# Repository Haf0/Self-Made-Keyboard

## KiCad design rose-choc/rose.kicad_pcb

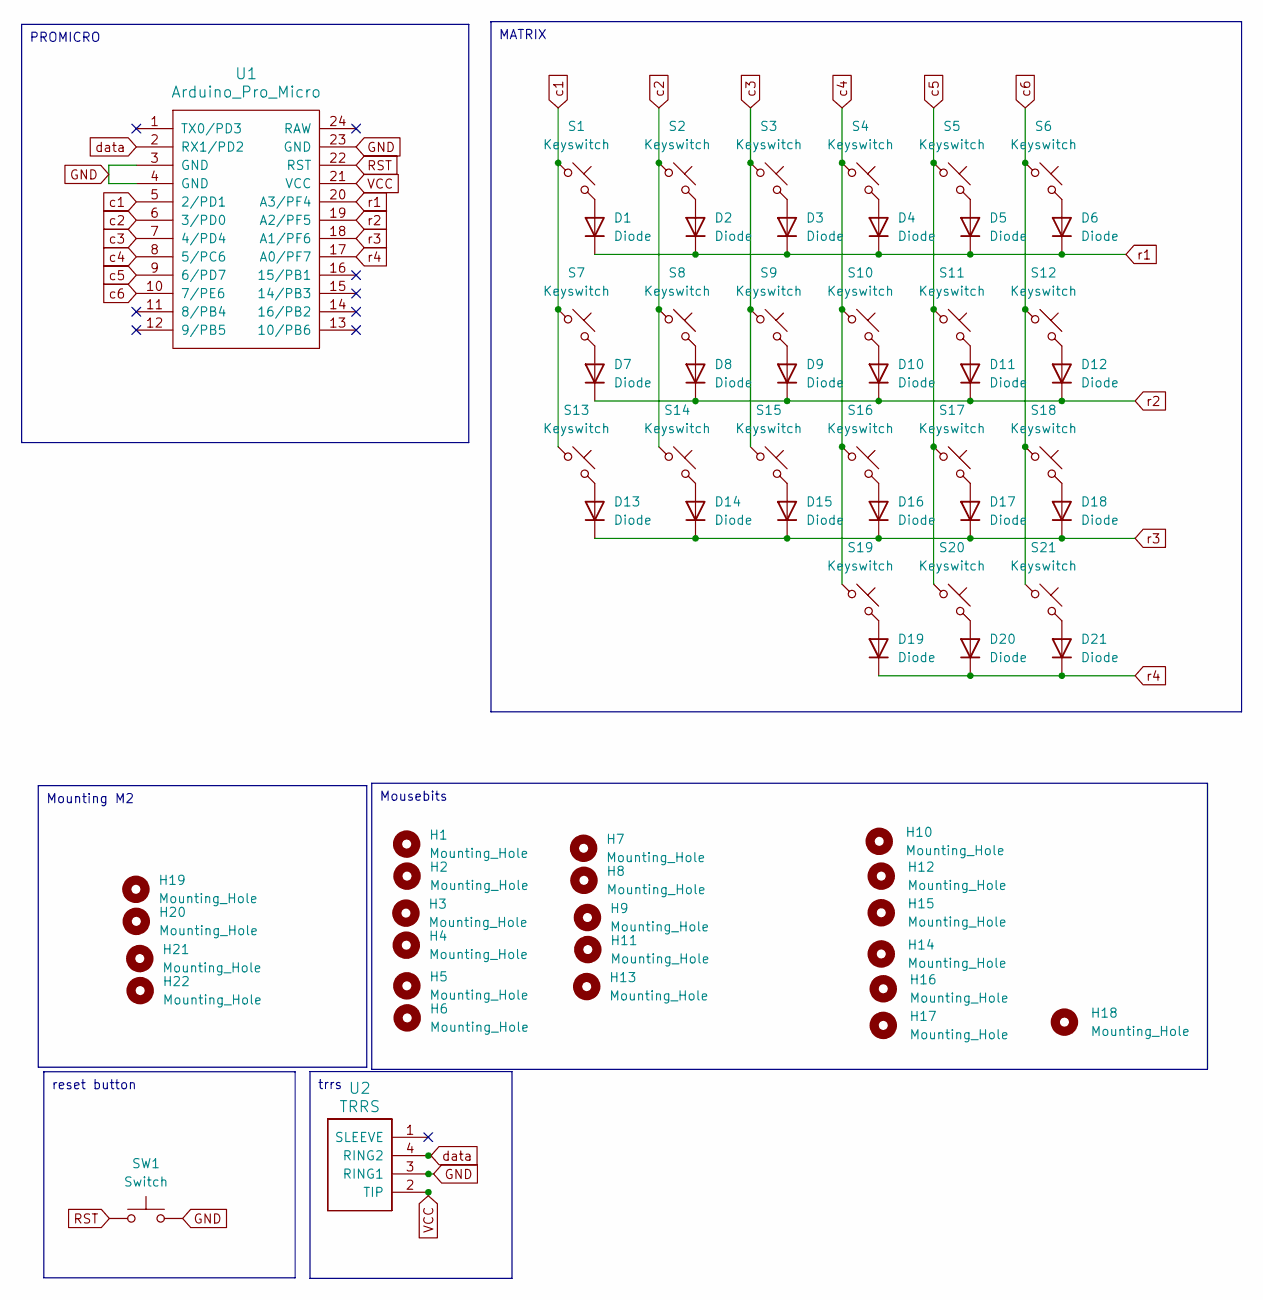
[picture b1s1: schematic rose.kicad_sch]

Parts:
D1, D2, D3, D4, D5, D6, D7, D8, D9, D10, D11, D12, D13, D14, D15, D16, D17, D18, D19, D20, D21: Diode; D3_SMD
H1, H2, H3, H4, H5, H6, H7, H8, H9, H10, H11, H12, H13, H14, H15, H16, H17, H18: Mounting_Hole; breakaway-hole
H19, H20, H21, H22: Mounting_Hole; M2_HOLE_v3
S1, S2, S3, S4, S5, S6, S7, S8, S9, S10, S11, S12, S13, S14, S15, S16, S17, S18, S19, S20, S21: Keyswitch; Choc
SW1: Switch; TACT_SWITCH_TVBP06
U1: Arduino_Pro_Micro; ProMicro_rev2
U2: TRRS; TRRS-PJ-320A-dual

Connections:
GND: SW1.2, U1.3 (GND), U1.4 (GND), U1.23 (GND), U2.3 (RING1)
unnamed: D1.2 (A), S1.2
unnamed: D2.2 (A), S2.2
unnamed: D3.2 (A), S3.2
unnamed: D4.2 (A), S4.2
unnamed: D5.2 (A), S5.2
unnamed: D6.2 (A), S6.2
unnamed: D7.2 (A), S7.2
unnamed: D8.2 (A), S8.2
unnamed: D9.2 (A), S9.2
unnamed: D10.2 (A), S10.2
unnamed: D11.2 (A), S11.2
unnamed: D12.2 (A), S12.2
unnamed: D13.2 (A), S13.2
unnamed: D14.2 (A), S14.2
unnamed: D15.2 (A), S15.2
unnamed: D16.2 (A), S16.2
unnamed: D17.2 (A), S17.2
unnamed: D18.2 (A), S18.2
unnamed: D19.2 (A), S19.2
unnamed: D20.2 (A), S20.2
unnamed: D21.2 (A), S21.2
RST: SW1.1, U1.22 (RST)
VCC: U1.21 (VCC), U2.2 (TIP)
c1: S1.1, S7.1, S13.1, U1.5 (2/PD1)
c2: S2.1, S8.1, S14.1, U1.6 (3/PD0)
c3: S3.1, S9.1, S15.1, U1.7 (4/PD4)
c4: S4.1, S10.1, S16.1, S19.1, U1.8 (5/PC6)
c5: S5.1, S11.1, S17.1, S20.1, U1.9 (6/PD7)
c6: S6.1, S12.1, S18.1, S21.1, U1.10 (7/PE6)
data: U1.2 (RX1/PD2), U2.4 (RING2)
r1: D1.1 (K), D2.1 (K), D3.1 (K), D4.1 (K), D5.1 (K), D6.1 (K), U1.20 (A3/PF4)
r2: D7.1 (K), D8.1 (K), D9.1 (K), D10.1 (K), D11.1 (K), D12.1 (K), U1.19 (A2/PF5)
r3: D13.1 (K), D14.1 (K), D15.1 (K), D16.1 (K), D17.1 (K), D18.1 (K), U1.18 (A1/PF6)
r4: D19.1 (K), D20.1 (K), D21.1 (K), U1.17 (A0/PF7)

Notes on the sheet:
trrs
PROMICRO
Mousebits
reset button
MATRIX
Mounting M2

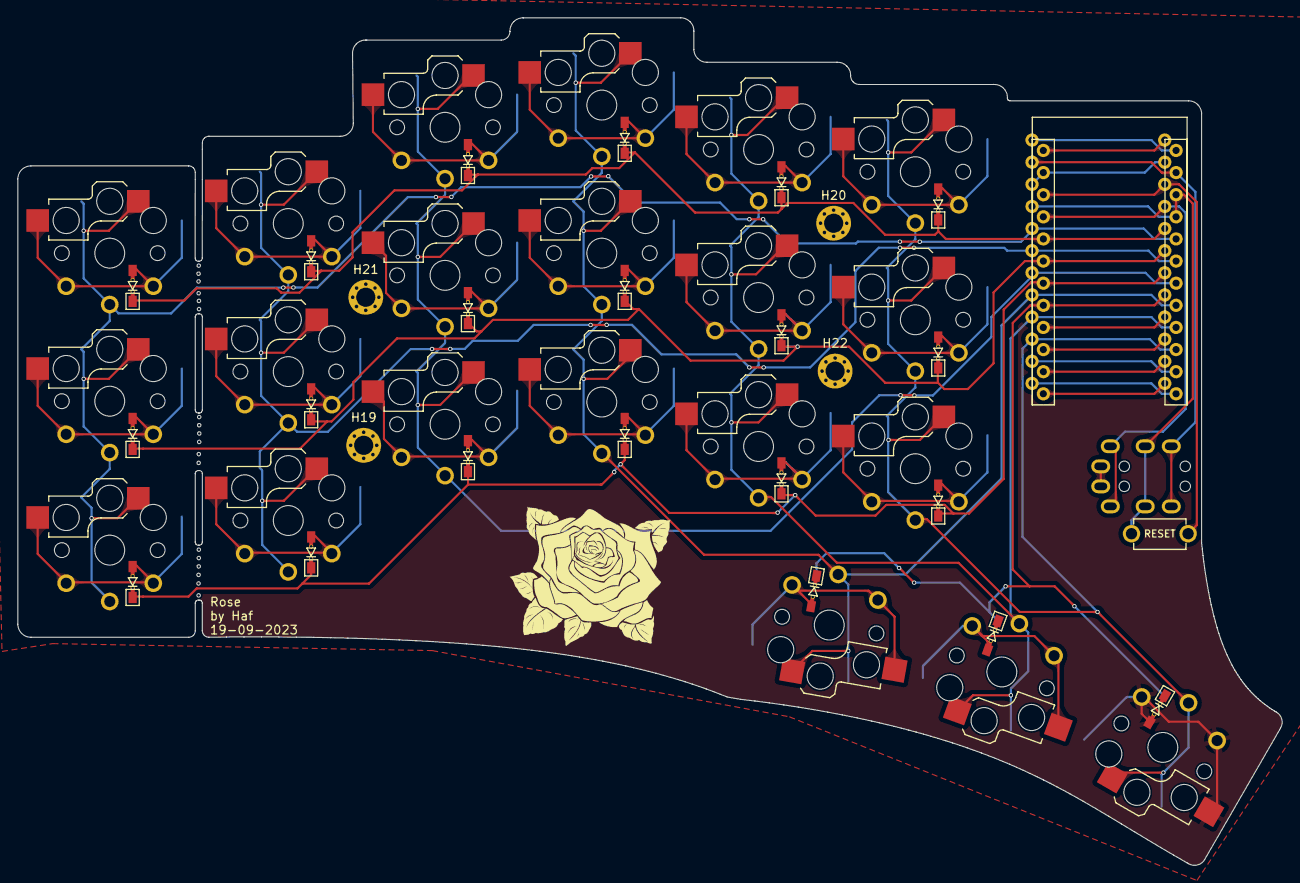
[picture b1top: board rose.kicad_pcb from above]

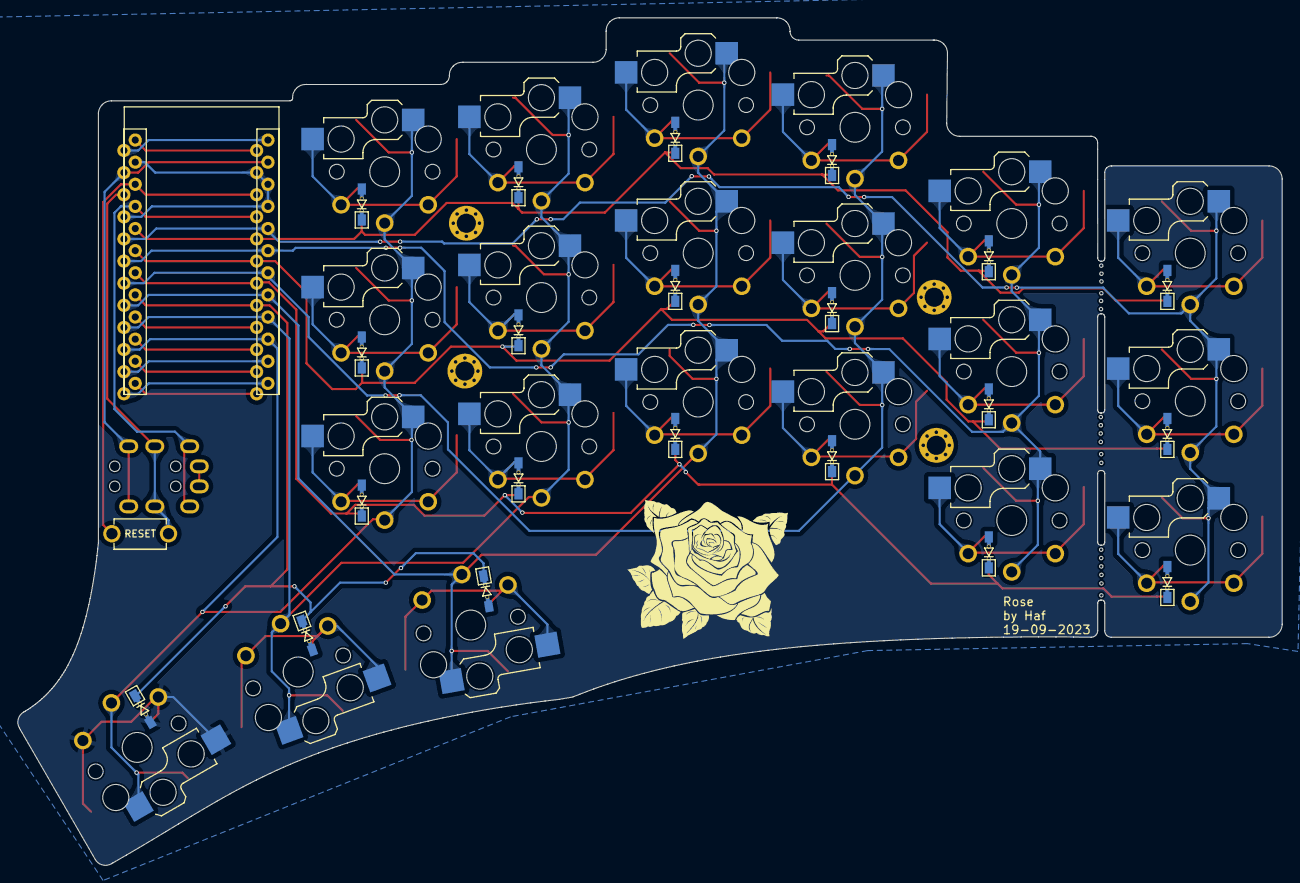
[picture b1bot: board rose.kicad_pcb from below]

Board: 2 copper layers, 145.2 x 97.3 mm, 67 parts (21 on the bottom side), 35 nets.

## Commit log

2023-09-19 commit rose keyboard v1.0
2023-09-19 add .gitignore
2023-09-19 rename folder
2023-09-19 rename project
2023-09-20 add assets for preview
2023-09-21 improve tracks and fix vias
2023-09-23 change diode footprint
2023-09-26 add the plate file
